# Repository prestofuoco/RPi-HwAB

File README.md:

# raspberry pi 5 hardware acceleration hat+ with xc7a

> **⚠️ work in progress:** this project is currently in the active pcb design and development phase. the hardware is not yet finalized or available. the repository structure, code, and documentation are placeholders for what is planned. stay tuned for updates!

## overview

welcome to the official repository for my raspberry pi 5 hat+ hardware accelerator. this project aims to create a powerful accelerator board featuring a xilinx artix-7 (xc7a) fpga. the goal is to bring high-speed, parallel processing capabilities to the raspberry pi 5, enabling a new generation of projects in fields like real-time signal processing, machine learning, and computer vision.

currently, the focus is on the **pcb design and layout**. the `pcb/` directory contains the most up-to-date work. other sections of this repository, such as `fpga_src` and `examples`, contain planned structures and will be developed once the hardware is stable.

## planned key features

* **xilinx artix-7 fpga:** will utilize the powerful and efficient xc7a series fpga for custom hardware acceleration
* **hat+ compliant:** designed to the latest raspberry pi hat+ specification for seamless integration and configuration
* **high-speed pcie interface:** aims to leverage the raspberry pi 5's pcie capabilities for maximum data throughput
* **on-board peripherals:** the design will include various peripherals which will be noted here
* **open-source design:** the pcb design, verilog/vhdl examples, and host software will be open-source and available in this repository

## hardware and software requirements (provisional)

### hardware

* a raspberry pi 5
* the final version of this xc7a fpga hat+ board
* a reliable power supply for the raspberry pi 5 (5v/5a recommended)

### software (provisional)

* **raspberry pi os:** ubuntu server 20.04+
* **xilinx vivado design suite:** for developing fpga bitstreams
* **kicad:** for viewing and editing the pcb design files

## project status

this project is currently focused on hardware development.

### 1. pcb design

the kicad project files can be found in the `pcb/` directory. this is the primary area of development right now. feedback and contributions for schematics and layout are welcome.

### 2. future steps (post-hardware)

once the pcb is finalized and fabricated, development will shift to:

1. **board bring-up and testing:** verifying all hardware components.
2. **fpga development:** creating example bitstreams (e.g., led blinker, pcie communication).
3. **host-side software:** writing drivers and libraries to communicate with the fpga from the raspberry pi.

## repository structure

```
.
├── bitstreams/       # (planned) pre-compiled fpga bitstream files
├── docs/             # (planned) detailed documentation and datasheets
├── examples/         # (planned) example projects (host-side code)
├── fpga_src/         # (backlog) verilog/vhdl source code for the fpga
│   └── RPi-HwAB-1/   # main vivado project files
│   └── test/         # pinout verification/experimentation
├── pcb/              # (active development) kicad/altium project files
│   └── simulations/  # ltspice simulation files
├── scripts/          # (planned) installation and helper scripts
├── utils/            # (planned) host-side utility programs
└── readme.md         # this file
```

## contact

andre winkel 14 [at] gmail [dot] com

andre [dot] winkel [at] email [dot] ucr [dot] edu

project link: [https://github.com/prestofuoco/rpi-hwab](https://github.com/prestofuoco/rpi-hwab)

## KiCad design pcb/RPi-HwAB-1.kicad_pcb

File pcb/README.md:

## schematic hierarchy structure
```
├── RPi-HwAB-1.kicad_sch                 # top-level schematic
│   └── main-pwr.kicad_sch               # quad-buck converter for fpga, I-sense networks
│   │	 └── sequencing.kicad_sch        # power sequencing for adp5054
│   │	 └── compensation.kicad_sch      # bulk decoupling and compensation networks for adp5054
│   └── fpga.kicad_sch                   # artix-7 35t abstraction
│   │    └── fpga-pwr.kicad_sch          # fpga power pins
│   │    │    └── decoupling.kicad_sch   # decoupling for fpga power rails
│   │    └── fpga-1.kicad_sch            # jtag, bank 14, bank 15
│   │    └── fpga-2.kicad_sch            # banks 16, 34, 35
│   │    └── fpga-3.kicad_sch            # mgt bank (216)
│   │    └── memory.kicad_sch            # spi flash / eeprom
│   └── sensors.kicad_sch                # temperature and current sensors
│   └── connectors.kicad_sch             # pcie, gpio, and jtag connectors
```

### top-level schematic as of january 4, 2026

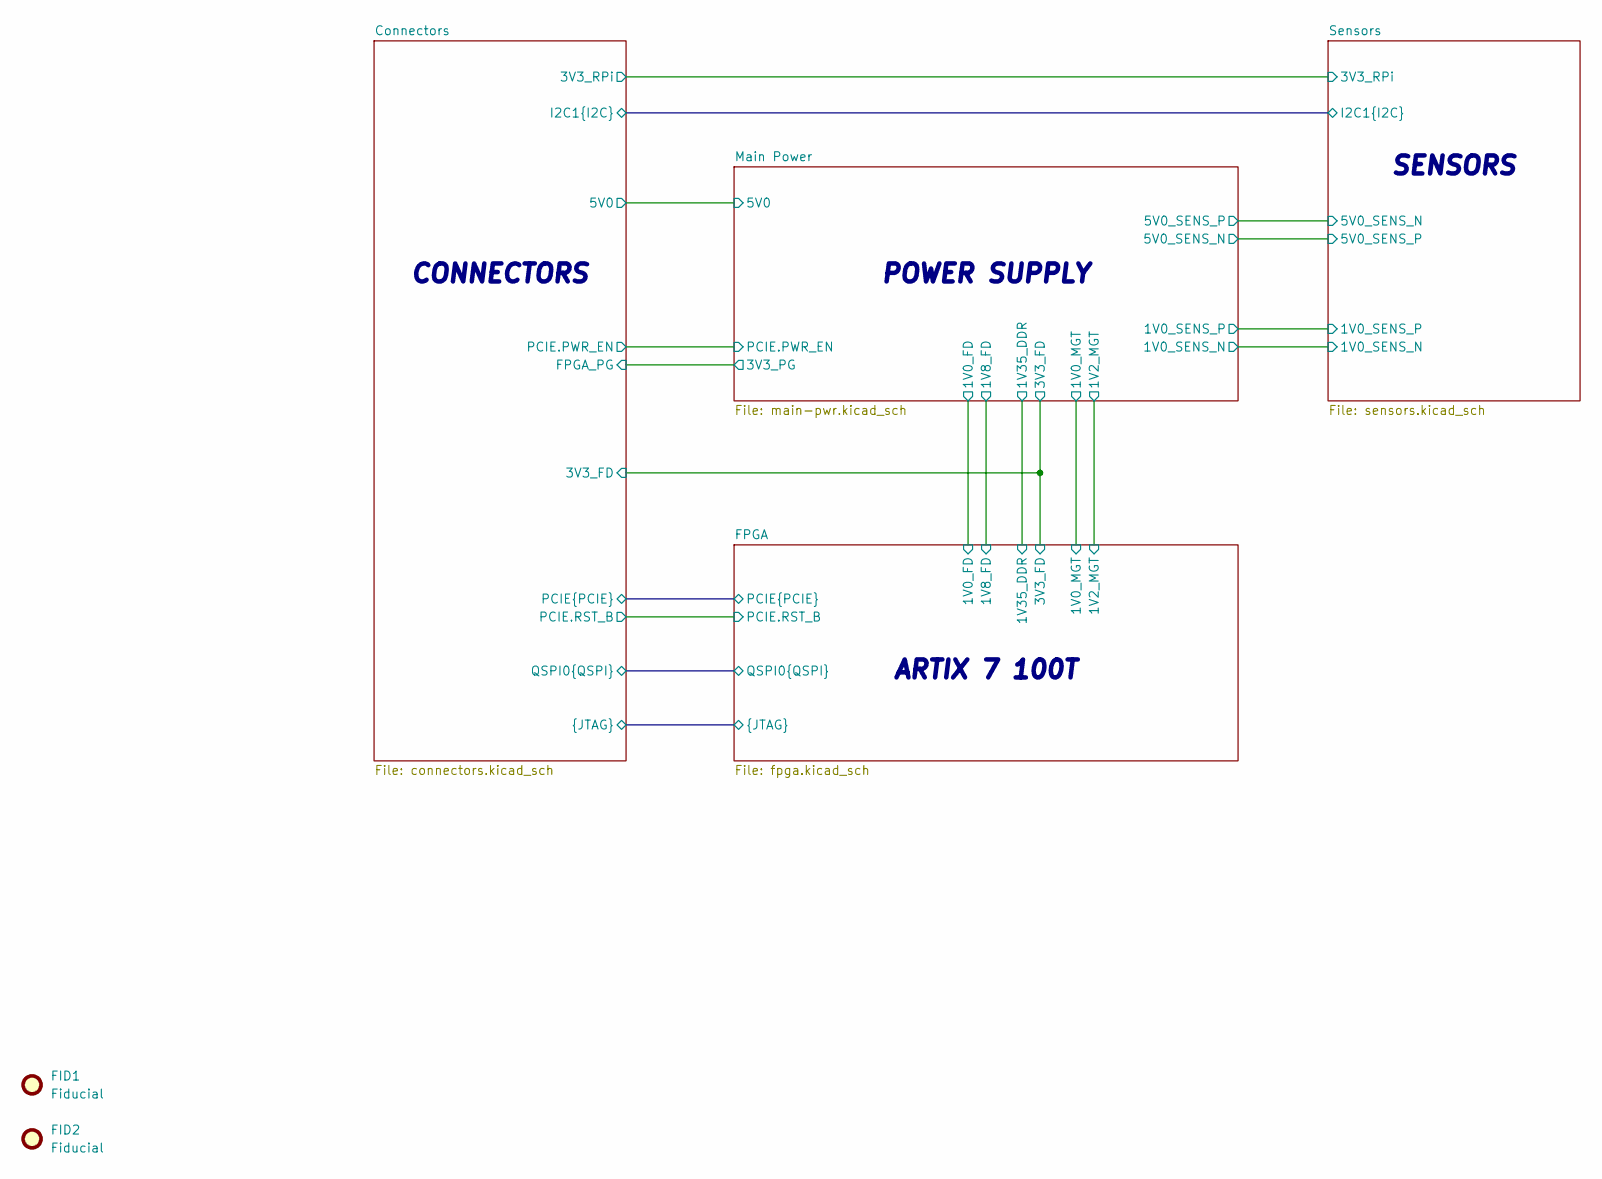
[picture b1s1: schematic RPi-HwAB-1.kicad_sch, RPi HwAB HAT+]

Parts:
FID1, FID2: Fiducial; Fiducial_1mm_Mask3mm

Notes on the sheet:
ARTIX 7 100T
SENSORS
CONNECTORS
POWER SUPPLY

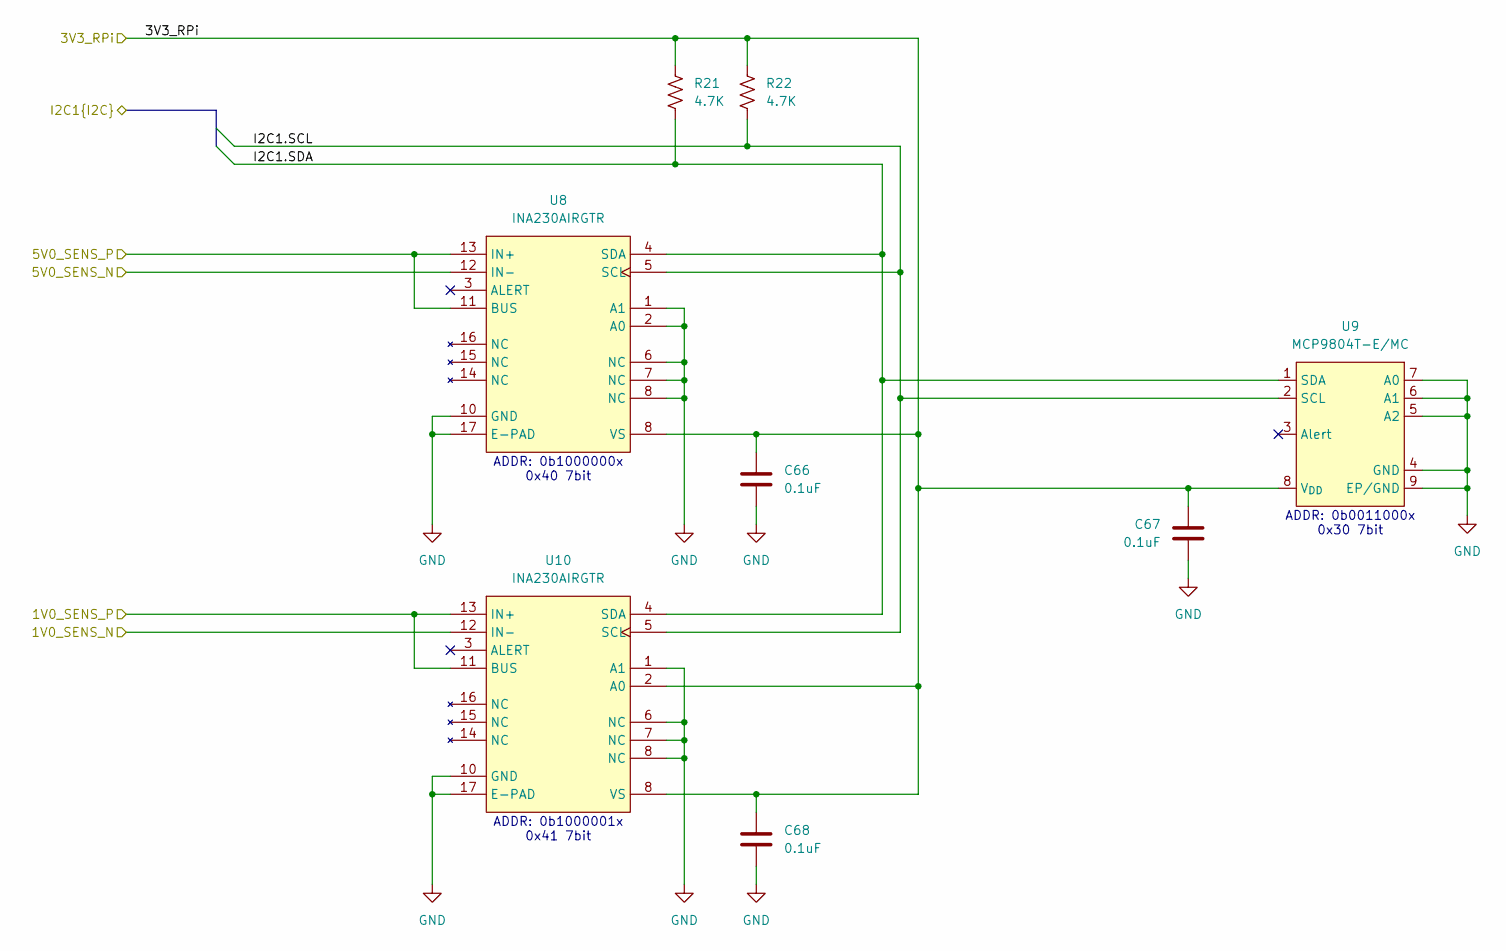
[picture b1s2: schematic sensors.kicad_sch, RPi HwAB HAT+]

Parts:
C66, C67, C68: 0.1uF; C_0402_1005Metric; Part Description CAP CER 0.1UF 16V X7R 0402
R21, R22: 4.7K; R_0402_1005Metric; Part Description RES 4.7K OHM 1% 1/16W 0402
U8, U10: INA230AIRGTR; VQFN-16-1EP_3x3mm_P0.5mm_EP1.6x1.6mm; Part Description IC CURRENT MONITOR 0.005 16VQFN
U9: MCP9804T-E/MC; DFN-8-1EP_3x2mm_P0.5mm_EP1.7x1.4mm; Part Description SENSOR DIGITAL -40C-125C 8DFN

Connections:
/Connectors/I2C1.SCL: R22.2, U8.5 (SCL), U9.2 (SCL), U10.5 (SCL); also elsewhere on the board
/Connectors/I2C1.SDA: R21.2, U8.4 (SDA), U9.1 (SDA), U10.4 (SDA); also elsewhere on the board
/Main Power/1V0_SENS_N: U10.12 (IN-); also elsewhere on the board
/Main Power/1V0_SENS_P: U10.11 (BUS), U10.13 (IN+); also elsewhere on the board
/Main Power/5V0_SENS_N: U8.11 (BUS), U8.13 (IN+); also elsewhere on the board
/Main Power/5V0_SENS_P: U8.12 (IN-); also elsewhere on the board

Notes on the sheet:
ADDR: 0b0011000x 0x30 7bit
ADDR: 0b1000001x 0x41 7bit
ADDR: 0b1000000x 0x40 7bit

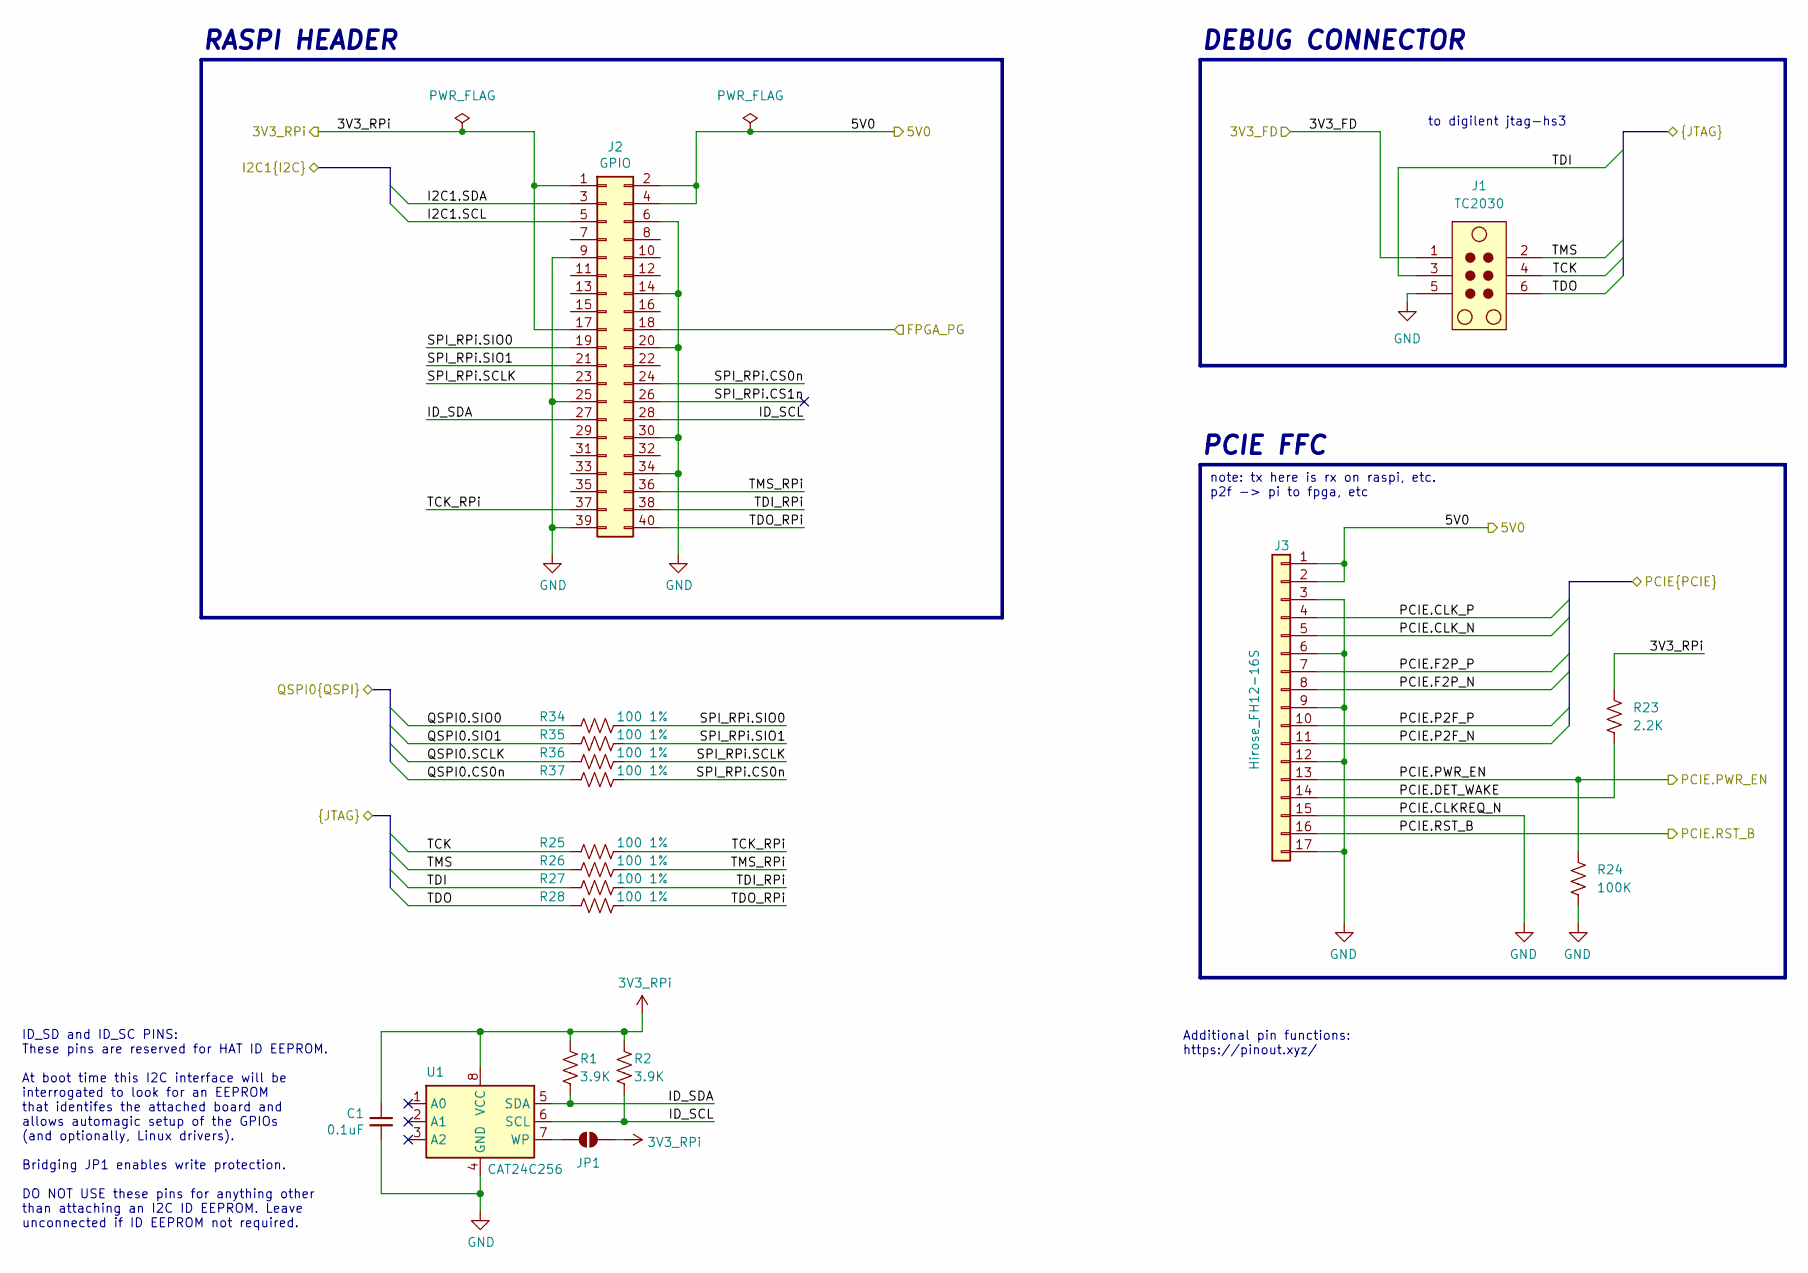
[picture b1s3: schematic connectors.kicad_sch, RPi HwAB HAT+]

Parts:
C1: 0.1uF; C_0402_1005Metric; Part Description CAP CER 0.1UF 16V X7R 0402
J1: TC2030; Tag-Connect_TC2030-IDC-NL_2x03_P1.27mm_Vertical
J2: GPIO; PinSocket_2x20_P2.54mm_Vertical; Part Description CONN RCPT 40POS 0.1 GOLD PCB
J3: Hirose_FH12-16S; Hirose_FH12-17S-0.5SH_1x17-1MP_P0.50mm_Horizontal; Part Description CONN FFC FPC BOTTOM 16POS 1MM RA
JP1: ID_WP; SolderJumper-2_P1.3mm_Open_Pad1.0x1.5mm
R1, R2: 3.9K; R_0402_1005Metric; Part Description RES 3.9K OHM 1% 1/16W 0402
R23: 2.2K; R_0402_1005Metric; Part Description RES 2.2K OHM 1% 1/16W 0402
R24: 100K; R_0402_1005Metric; Part Description RES 100K OHM 1% 1/16W 0402
R25, R26, R27, R28, R34, R35, R36, R37: 100 1%; R_0402_1005Metric; Part Description RES SMD 100 OHM 1% 1/5W 0402
U1: CAT24C256; DFN-8-1EP_3x2mm_P0.5mm_EP1.7x1.4mm; Part Description IC EEPROM 256KBIT I2C 1MHZ 8UDFN

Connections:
/Connectors/3V3_FD: J1.1; also elsewhere on the board
/Connectors/5V0: J2.2, J2.4, J3.1, J3.2; also elsewhere on the board
/Connectors/I2C1.SCL: J2.5; also elsewhere on the board
/Connectors/I2C1.SDA: J2.3; also elsewhere on the board
/Connectors/ID_SCL: J2.28, R2.2, U1.6 (SCL)
/Connectors/ID_SDA: J2.27, R1.2, U1.5 (SDA)
/Connectors/PCIE.CLK_N: J3.5; also elsewhere on the board
/Connectors/PCIE.CLK_P: J3.4; also elsewhere on the board
/Connectors/PCIE.DET_WAKE: J3.14, R23.2
/Connectors/PCIE.F2P_N: J3.8; also elsewhere on the board
/Connectors/PCIE.F2P_P: J3.7; also elsewhere on the board
/Connectors/PCIE.P2F_N: J3.11; also elsewhere on the board
/Connectors/PCIE.P2F_P: J3.10; also elsewhere on the board
/Connectors/PCIE.PWR_EN: J3.13, R24.2; also elsewhere on the board
/Connectors/PCIE.RST_B: J3.16; also elsewhere on the board
/Connectors/QSPI0.CS0n: R37.1; also elsewhere on the board
/Connectors/QSPI0.SCLK: R36.1; also elsewhere on the board
/Connectors/QSPI0.SIO0: R34.1; also elsewhere on the board
/Connectors/QSPI0.SIO1: R35.1; also elsewhere on the board
/Connectors/SPI_RPi.CS0n: J2.24, R37.2
/Connectors/SPI_RPi.CS1n: J2.26
/Connectors/SPI_RPi.SCLK: J2.23, R36.2
/Connectors/SPI_RPi.SIO0: J2.19, R34.2
/Connectors/SPI_RPi.SIO1: J2.21, R35.2
/Connectors/TCK: J1.4, R25.1; also elsewhere on the board
/Connectors/TCK_RPi: J2.37, R25.2
/Connectors/TDI: J1.3, R27.1; also elsewhere on the board
/Connectors/TDI_RPi: J2.38, R27.2
/Connectors/TDO: J1.6, R28.1; also elsewhere on the board
/Connectors/TDO_RPi: J2.40, R28.2
/Connectors/TMS: J1.2, R26.1; also elsewhere on the board
/Connectors/TMS_RPi: J2.36, R26.2
/Main Power/3V3_PG: J2.18; also elsewhere on the board
unnamed: JP1.1 (A), U1.7 (WP)

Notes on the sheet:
PCIE FFC
note: tx here is rx on raspi, etc. p2f -> pi to fpga, etc
Additional pin functions: https://pinout.xyz/
RASPI HEADER
ID_SD and ID_SC PINS: These pins are reserved for HAT ID EEPROM. At boot time this I2C interface will be interrogated to look for an EEPROM that identifes the attached board and allows automagic setup of the GPIOs (and optionally, Linux drivers). Bridging JP1 enables write protection. DO NOT USE th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
DEBUG CONNECTOR
to digilent jtag-hs3

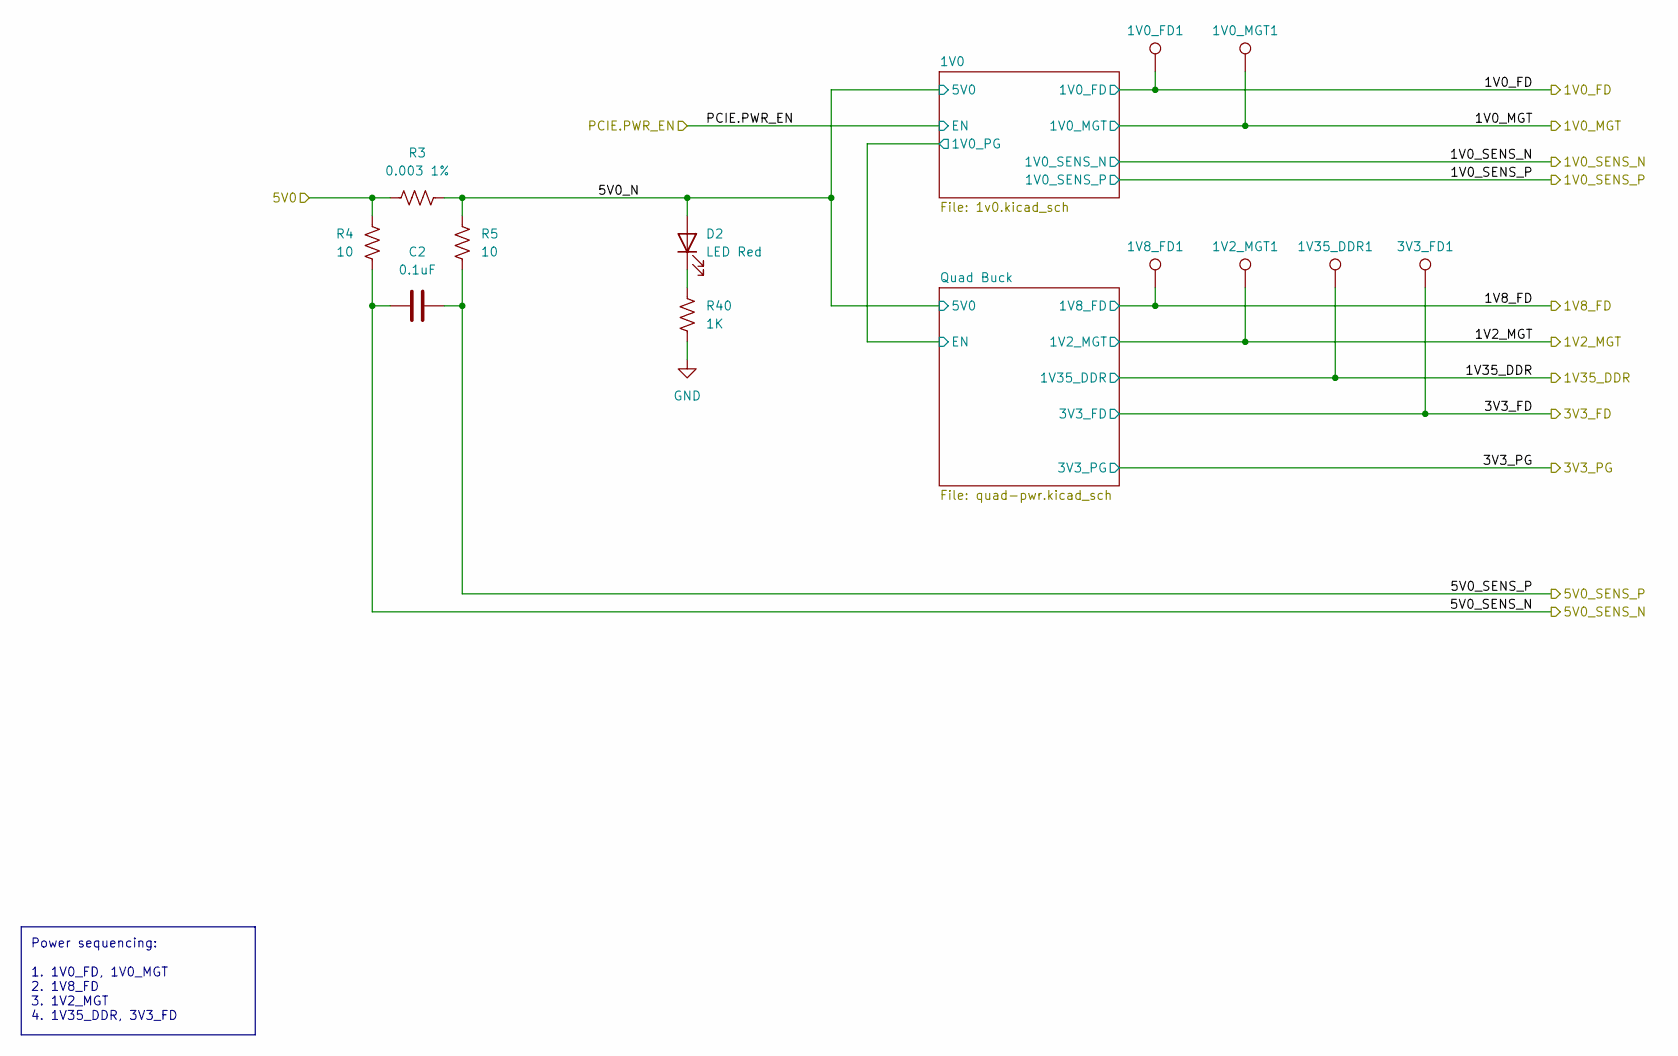
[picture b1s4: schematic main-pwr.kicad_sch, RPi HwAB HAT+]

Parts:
1V0_FD1, 1V0_MGT1, 1V2_MGT1, 1V8_FD1, 1V35_DDR1, 3V3_FD1: TestPoint; TestPoint_Pad_D1.0mm
C2: 0.1uF; C_0402_1005Metric; Part Description CAP CER 0.1UF 16V X7R 0402
D2: LED Red; LED_0603_1608Metric; Part Description LED RED CLEAR CHIP SMD
R3: 0.003 1%; R_1206_3216Metric; Part Description WSKW0612 .003 1% EA E3
R4, R5: 10; R_0402_1005Metric; Part Description RES 10 OHM 1% 1/16W 0402
R40: 1K; R_0402_1005Metric; Part Description RES 1K OHM 5% 1/16W 0402

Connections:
/Connectors/5V0: R3.1, R4.2; also elsewhere on the board
/Main Power/5V0_N: D2.2 (A), R3.2, R5.2; also elsewhere on the board
/Main Power/5V0_SENS_N: C2.1, R4.1; also elsewhere on the board
/Main Power/5V0_SENS_P: C2.2, R5.1; also elsewhere on the board
unnamed: D2.1 (K), R40.1

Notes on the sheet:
Power sequencing: 1. 1V0_FD, 1V0_MGT 2. 1V8_FD 3. 1V2_MGT 4. 1V35_DDR, 3V3_FD

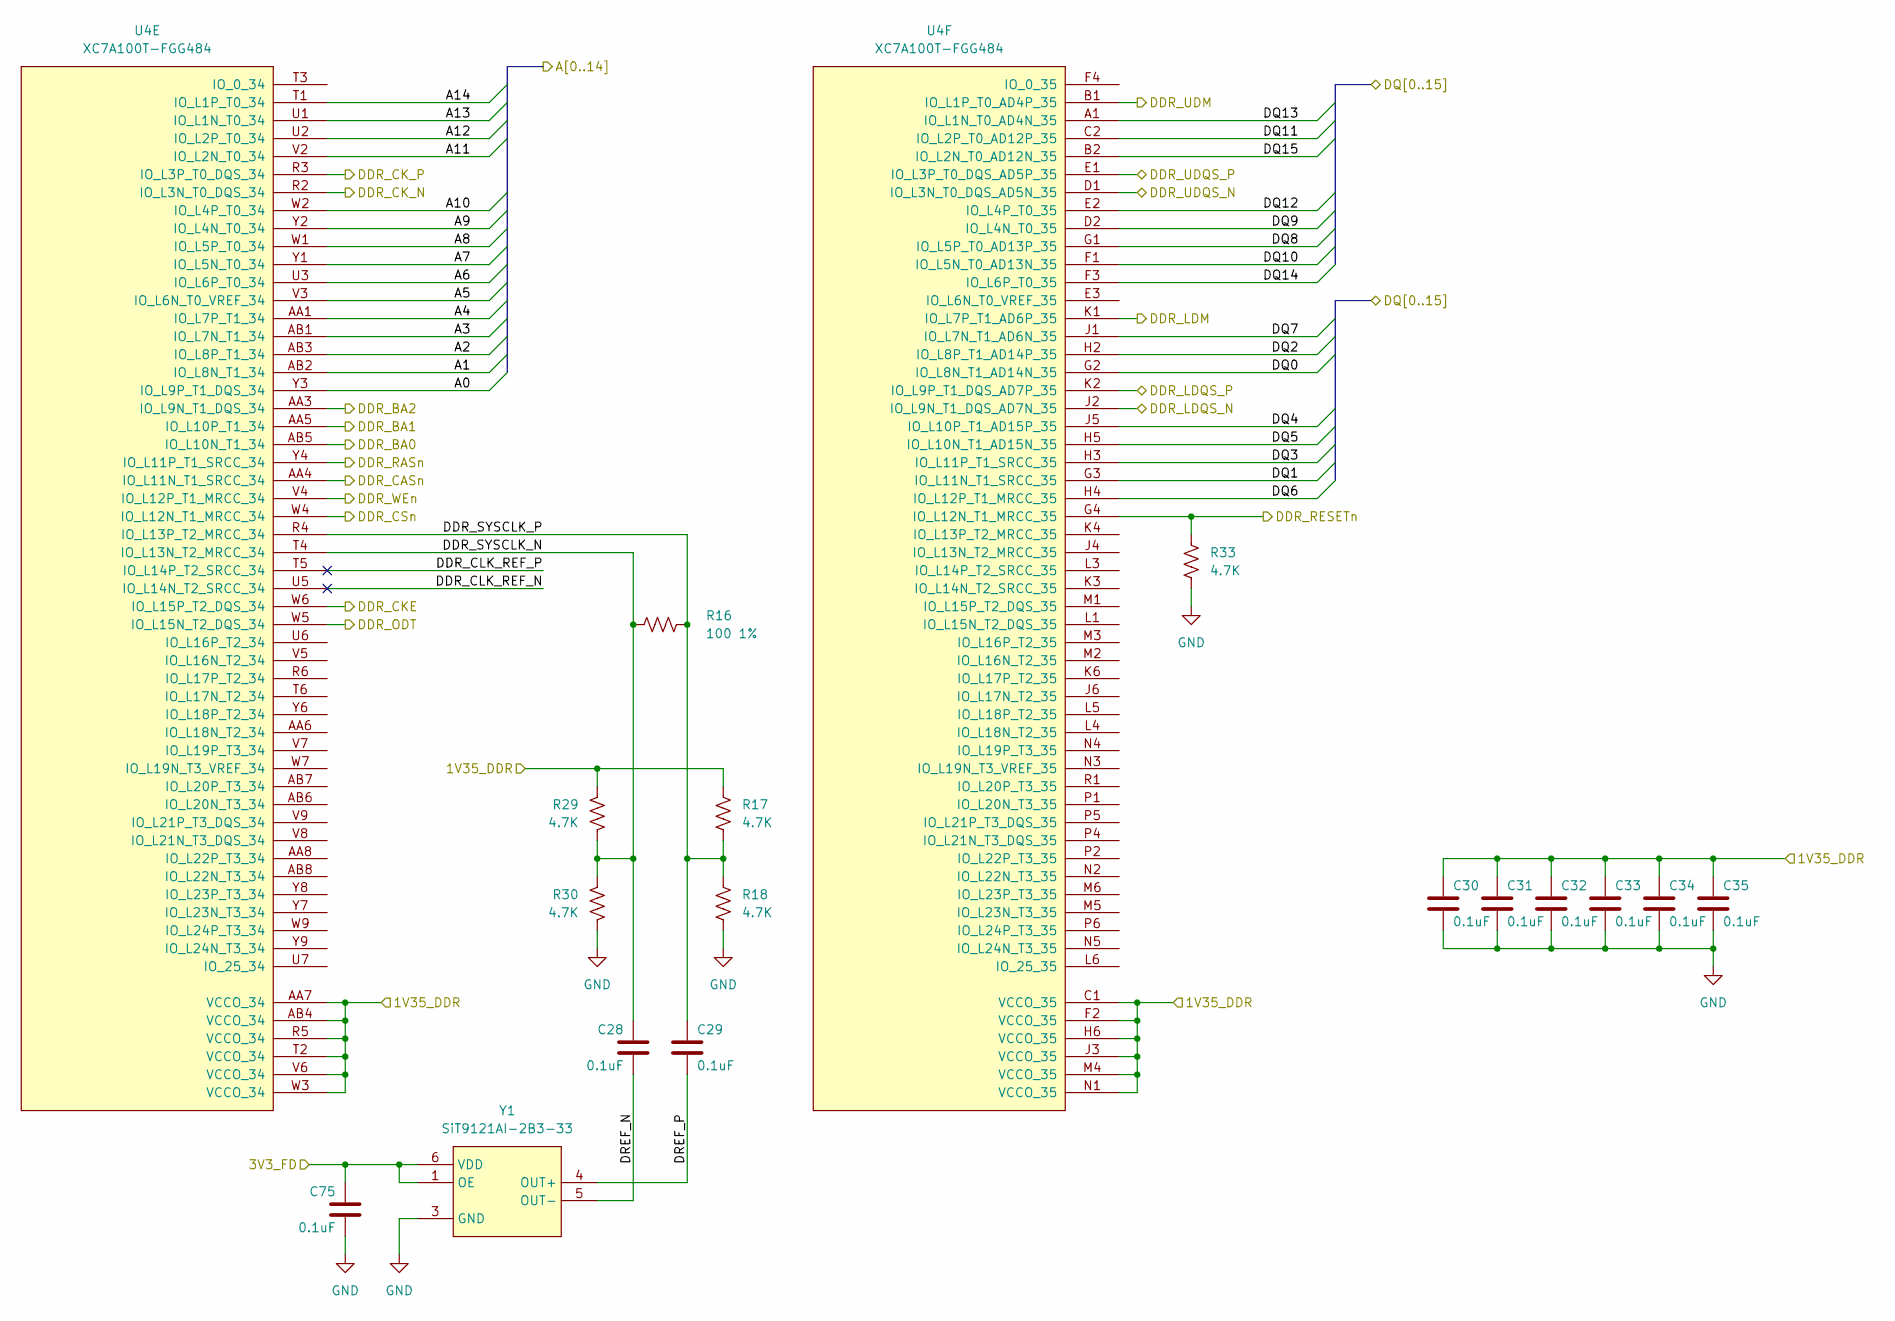
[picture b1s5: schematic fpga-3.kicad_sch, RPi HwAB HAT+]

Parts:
C28, C29, C30, C31, C32, C33, C34, C35, C75: 0.1uF; C_0402_1005Metric; Part Description CAP CER 0.1UF 16V X7R 0402
R16: 100 1%; R_0402_1005Metric; Part Description RES SMD 100 OHM 1% 1/5W 0402
R17, R18, R29, R30, R33: 4.7K; R_0402_1005Metric; Part Description RES 4.7K OHM 1% 1/16W 0402
U4: XC7A100T-FGG484; Xilinx_FGG484; Part Description IC FPGA 285 I/O 484FBGA
Y1: SiT9121AI-2B3-33; Oscillator_SMD_SiTime_PQFD-6L_3.2x2.5mm; Part Description MEMS OSC XO 156.2500MHZ LVDS SMD

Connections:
/Connectors/3V3_FD: C75.2, Y1.1 (OE), Y1.6 (VDD); also elsewhere on the board
/FPGA/FPGA 34, 35/A0: U4.Y3 (IO_L9P_T1_DQS_34); also elsewhere on the board
/FPGA/FPGA 34, 35/A1: U4.AB2 (IO_L8N_T1_34); also elsewhere on the board
/FPGA/FPGA 34, 35/A2: U4.AB3 (IO_L8P_T1_34); also elsewhere on the board
/FPGA/FPGA 34, 35/A3: U4.AB1 (IO_L7N_T1_34); also elsewhere on the board
/FPGA/FPGA 34, 35/A4: U4.AA1 (IO_L7P_T1_34); also elsewhere on the board
/FPGA/FPGA 34, 35/A5: U4.V3 (IO_L6N_T0_VREF_34); also elsewhere on the board
/FPGA/FPGA 34, 35/A6: U4.U3 (IO_L6P_T0_34); also elsewhere on the board
/FPGA/FPGA 34, 35/A7: U4.Y1 (IO_L5N_T0_34); also elsewhere on the board
/FPGA/FPGA 34, 35/A8: U4.W1 (IO_L5P_T0_34); also elsewhere on the board
/FPGA/FPGA 34, 35/A9: U4.Y2 (IO_L4N_T0_34); also elsewhere on the board
/FPGA/FPGA 34, 35/A10: U4.W2 (IO_L4P_T0_34); also elsewhere on the board
/FPGA/FPGA 34, 35/A11: U4.V2 (IO_L2N_T0_34); also elsewhere on the board
/FPGA/FPGA 34, 35/A12: U4.U2 (IO_L2P_T0_34); also elsewhere on the board
/FPGA/FPGA 34, 35/A13: U4.U1 (IO_L1N_T0_34); also elsewhere on the board
/FPGA/FPGA 34, 35/A14: U4.T1 (IO_L1P_T0_34); also elsewhere on the board
/FPGA/FPGA 34, 35/DDR_BA0: U4.AB5 (IO_L10N_T1_34); also elsewhere on the board
/FPGA/FPGA 34, 35/DDR_BA1: U4.AA5 (IO_L10P_T1_34); also elsewhere on the board
/FPGA/FPGA 34, 35/DDR_BA2: U4.AA3 (IO_L9N_T1_DQS_34); also elsewhere on the board
/FPGA/FPGA 34, 35/DDR_CASn: U4.AA4 (IO_L11N_T1_SRCC_34); also elsewhere on the board
/FPGA/FPGA 34, 35/DDR_CKE: U4.W6 (IO_L15P_T2_DQS_34); also elsewhere on the board
/FPGA/FPGA 34, 35/DDR_CK_N: U4.R2 (IO_L3N_T0_DQS_34); also elsewhere on the board
/FPGA/FPGA 34, 35/DDR_CK_P: U4.R3 (IO_L3P_T0_DQS_34); also elsewhere on the board
/FPGA/FPGA 34, 35/DDR_CLK_REF_N: U4.U5 (IO_L14N_T2_SRCC_34)
/FPGA/FPGA 34, 35/DDR_CLK_REF_P: U4.T5 (IO_L14P_T2_SRCC_34)
/FPGA/FPGA 34, 35/DDR_CSn: U4.W4 (IO_L12N_T1_MRCC_34); also elsewhere on the board
/FPGA/FPGA 34, 35/DDR_LDM: U4.K1 (IO_L7P_T1_AD6P_35); also elsewhere on the board
/FPGA/FPGA 34, 35/DDR_LDQS_N: U4.J2 (IO_L9N_T1_DQS_AD7N_35); also elsewhere on the board
/FPGA/FPGA 34, 35/DDR_LDQS_P: U4.K2 (IO_L9P_T1_DQS_AD7P_35); also elsewhere on the board
/FPGA/FPGA 34, 35/DDR_ODT: U4.W5 (IO_L15N_T2_DQS_34); also elsewhere on the board
/FPGA/FPGA 34, 35/DDR_RASn: U4.Y4 (IO_L11P_T1_SRCC_34); also elsewhere on the board
/FPGA/FPGA 34, 35/DDR_RESETn: R33.1, U4.G4 (IO_L12N_T1_MRCC_35); also elsewhere on the board
/FPGA/FPGA 34, 35/DDR_SYSCLK_N: C28.1, R16.1, R29.2, R30.1, U4.T4 (IO_L13N_T2_MRCC_34)
/FPGA/FPGA 34, 35/DDR_SYSCLK_P: C29.1, R16.2, R17.2, R18.1, U4.R4 (IO_L13P_T2_MRCC_34)
/FPGA/FPGA 34, 35/DDR_UDM: U4.B1 (IO_L1P_T0_AD4P_35); also elsewhere on the board
/FPGA/FPGA 34, 35/DDR_UDQS_N: U4.D1 (IO_L3N_T0_DQS_AD5N_35); also elsewhere on the board
/FPGA/FPGA 34, 35/DDR_UDQS_P: U4.E1 (IO_L3P_T0_DQS_AD5P_35); also elsewhere on the board
/FPGA/FPGA 34, 35/DDR_WEn: U4.V4 (IO_L12P_T1_MRCC_34); also elsewhere on the board
/FPGA/FPGA 34, 35/DQ0: U4.G2 (IO_L8N_T1_AD14N_35); also elsewhere on the board
/FPGA/FPGA 34, 35/DQ1: U4.G3 (IO_L11N_T1_SRCC_35); also elsewhere on the board
/FPGA/FPGA 34, 35/DQ2: U4.H2 (IO_L8P_T1_AD14P_35); also elsewhere on the board
/FPGA/FPGA 34, 35/DQ3: U4.H3 (IO_L11P_T1_SRCC_35); also elsewhere on the board
/FPGA/FPGA 34, 35/DQ4: U4.J5 (IO_L10P_T1_AD15P_35); also elsewhere on the board
/FPGA/FPGA 34, 35/DQ5: U4.H5 (IO_L10N_T1_AD15N_35); also elsewhere on the board
/FPGA/FPGA 34, 35/DQ6: U4.H4 (IO_L12P_T1_MRCC_35); also elsewhere on the board
/FPGA/FPGA 34, 35/DQ7: U4.J1 (IO_L7N_T1_AD6N_35); also elsewhere on the board
/FPGA/FPGA 34, 35/DQ8: U4.G1 (IO_L5P_T0_AD13P_35); also elsewhere on the board
/FPGA/FPGA 34, 35/DQ9: U4.D2 (IO_L4N_T0_35); also elsewhere on the board
/FPGA/FPGA 34, 35/DQ10: U4.F1 (IO_L5N_T0_AD13N_35); also elsewhere on the board
/FPGA/FPGA 34, 35/DQ11: U4.C2 (IO_L2P_T0_AD12P_35); also elsewhere on the board
/FPGA/FPGA 34, 35/DQ12: U4.E2 (IO_L4P_T0_35); also elsewhere on the board
/FPGA/FPGA 34, 35/DQ13: U4.A1 (IO_L1N_T0_AD4N_35); also elsewhere on the board
/FPGA/FPGA 34, 35/DQ14: U4.F3 (IO_L6P_T0_35); also elsewhere on the board
/FPGA/FPGA 34, 35/DQ15: U4.B2 (IO_L2N_T0_AD12N_35); also elsewhere on the board
/FPGA/FPGA 34, 35/DREF_N: C28.2, Y1.5 (OUT-)
/FPGA/FPGA 34, 35/DREF_P: C29.2, Y1.4 (OUT+)
/Main Power/1V35_DDR: C30.2, C31.2, C32.2, C33.2, C34.2, C35.2, R17.1, R29.1, U4.AA7 (VCCO_34), U4.AB4 (VCCO_34), U4.C1 (VCCO_35), U4.F2 (VCCO_35), U4.H6 (VCCO_35), U4.J3 (VCCO_35), U4.M4 (VCCO_35), U4.N1 (VCCO_35), U4.R5 (VCCO_34), U4.T2 (VCCO_34), U4.V6 (VCCO_34), U4.W3 (VCCO_34); also elsewhere on the board

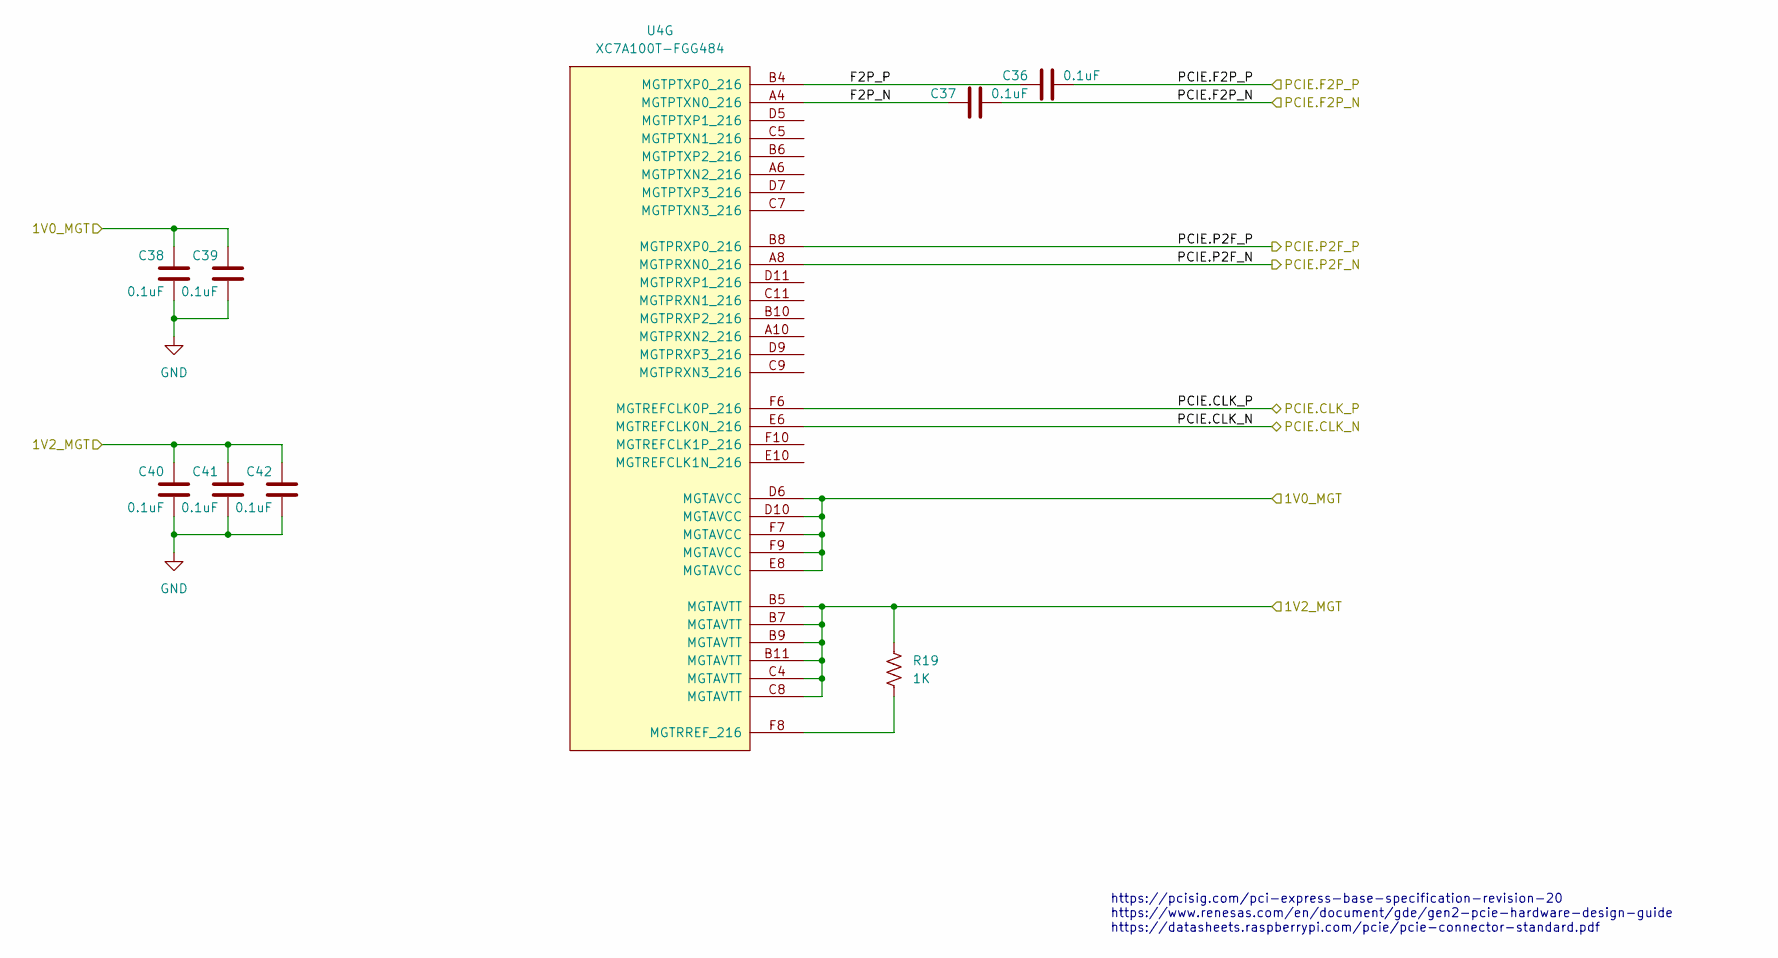
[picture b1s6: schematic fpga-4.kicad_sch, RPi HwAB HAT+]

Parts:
C36, C37, C38, C39, C40, C41, C42: 0.1uF; C_0402_1005Metric; Part Description CAP CER 0.1UF 16V X7R 0402
R19: 1K; R_0402_1005Metric; Part Description RES 1K OHM 5% 1/16W 0402
U4: XC7A100T-FGG484; Xilinx_FGG484; Part Description IC FPGA 285 I/O 484FBGA

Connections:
/Connectors/PCIE.CLK_N: U4.F6 (MGTREFCLK0P_216); also elsewhere on the board
/Connectors/PCIE.CLK_P: U4.E6 (MGTREFCLK0N_216); also elsewhere on the board
/Connectors/PCIE.F2P_N: C36.2; also elsewhere on the board
/Connectors/PCIE.F2P_P: C37.2; also elsewhere on the board
/Connectors/PCIE.P2F_N: U4.B8 (MGTPRXP0_216); also elsewhere on the board
/Connectors/PCIE.P2F_P: U4.A8 (MGTPRXN0_216); also elsewhere on the board
/FPGA/FPGA 216/F2P_N: C37.1, U4.A4 (MGTPTXN0_216)
/FPGA/FPGA 216/F2P_P: C36.1, U4.B4 (MGTPTXP0_216)
/Main Power/1V0_MGT: C38.2, C39.2, U4.D6 (MGTAVCC), U4.D10 (MGTAVCC), U4.E8 (MGTAVCC), U4.F7 (MGTAVCC), U4.F9 (MGTAVCC); also elsewhere on the board
/Main Power/1V2_MGT: C40.2, C41.2, C42.2, R19.2, U4.B5 (MGTAVTT), U4.B7 (MGTAVTT), U4.B9 (MGTAVTT), U4.B11 (MGTAVTT), U4.C4 (MGTAVTT), U4.C8 (MGTAVTT); also elsewhere on the board
unnamed: R19.1, U4.F8 (MGTRREF_216)

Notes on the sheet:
https://pcisig.com/pci-express-base-specification-revision-20 https://www.renesas.com/en/document/gde/gen2-pcie-hardware-design-guide https://datasheets.raspberrypi.com/pcie/pcie-connector-standard.pdf
